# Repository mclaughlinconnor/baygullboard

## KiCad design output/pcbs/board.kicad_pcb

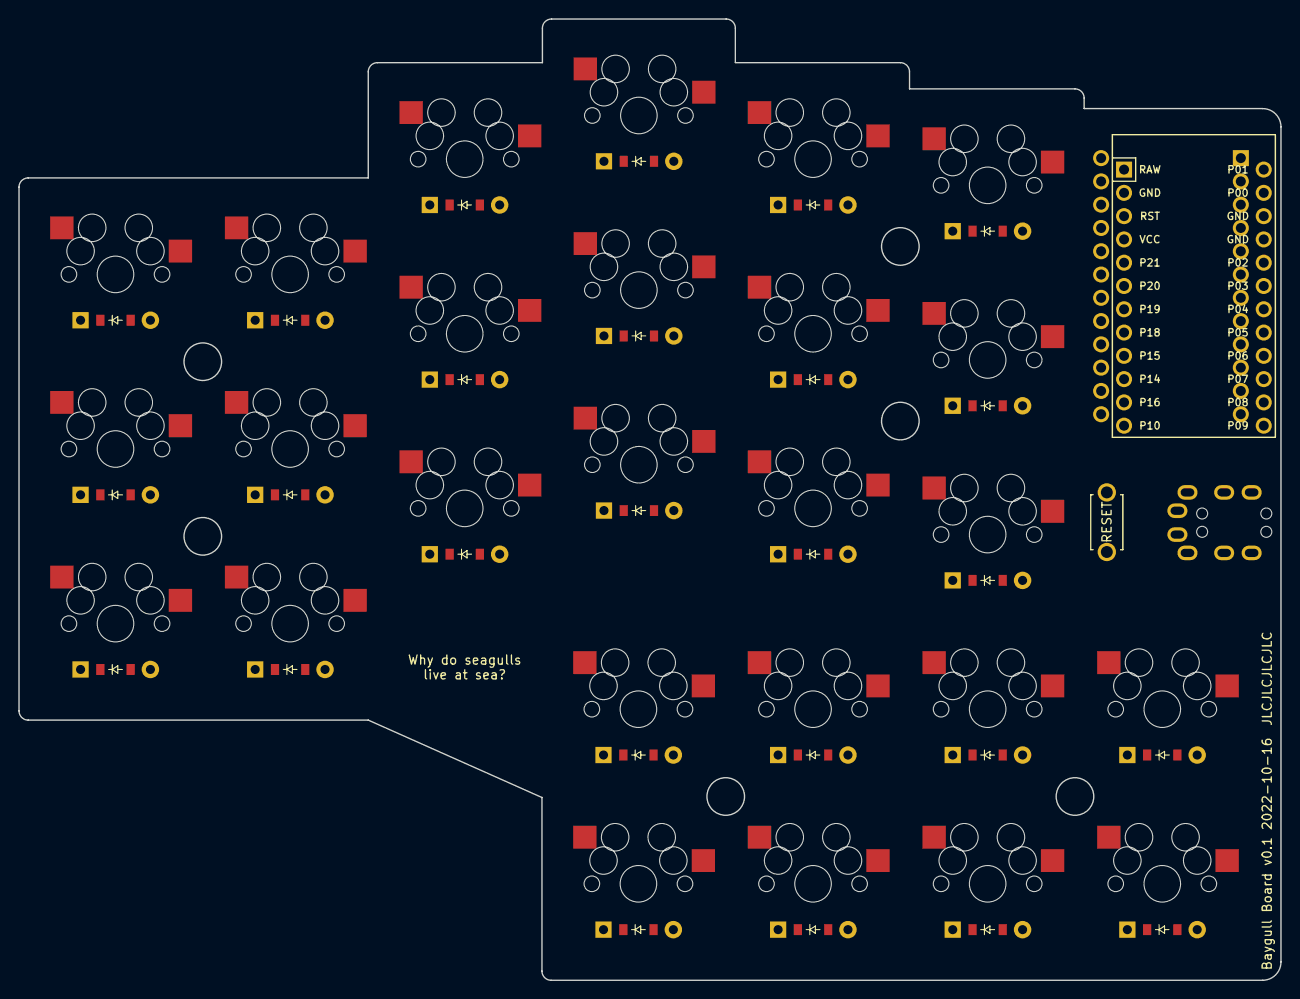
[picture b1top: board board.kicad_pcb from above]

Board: 2 copper layers, 137.7 x 104.9 mm, 57 parts (0 on the bottom side), 48 nets, no tracks yet.

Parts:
B1: ResetSW
D1, D2, D3, D4, D5, D6, D7, D8, D9, D10, D11, D12, D13, D14, D15, D16, D17, D18, D19, D20, D21, D22, D23, D24, D25, D26: ComboDiode
MCU1, MCU2: ProMicro
S1, S2, S3, S4, S5, S6, S7, S8, S9, S10, S11, S12, S13, S14, S15, S16, S17, S18, S19, S20, S21, S22, S23, S24, S25, S26: MX
TRRS1, TRRS2: TRRS-PJ-320A-dual

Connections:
GND: B1.2, MCU1.2, MCU1.15, MCU1.16, MCU2.2, MCU2.15, MCU2.16, TRRS1.3, TRRS2.3
P0: MCU1.14, MCU2.14, TRRS1.4, TRRS2.4
P1: MCU1.13, MCU2.13
P2: MCU1.17, MCU2.17
P3: MCU1.18, MCU2.18
P4: D3.1, D3.2, D6.1, D6.2, D9.1, D9.2, D12.1, D12.2, D15.1, D15.2, D18.1, D18.2, MCU1.19, MCU2.19
P5: D2.1, D2.2, D5.1, D5.2, D8.1, D8.2, D11.1, D11.2, D14.1, D14.2, D17.1, D17.2, MCU1.20, MCU2.20
P6: D1.1, D1.2, D4.1, D4.2, D7.1, D7.2, D10.1, D10.2, D13.1, D13.2, D16.1, D16.2, MCU1.21, MCU2.21
P7: D19.1, D19.2, D20.1, D20.2, D21.1, D21.2, D22.1, D22.2, D23.1, D23.2, D24.1, D24.2, D25.1, D25.2, D26.1, D26.2, MCU1.22, MCU2.22
P8: MCU1.23, MCU2.23
P9: MCU1.24, MCU2.24
P10: MCU1.12, MCU2.12
P14: MCU1.10, MCU2.10, S16.2, S17.2, S18.2, S24.2
P15: MCU1.9, MCU2.9, S13.2, S14.2, S15.2, S23.2
P16: MCU1.11, MCU2.11
P18: MCU1.8, MCU2.8, S10.2, S11.2, S12.2, S19.2, S20.2
P19: MCU1.7, MCU2.7, S7.2, S8.2, S9.2, S21.2, S22.2
P20: MCU1.6, MCU2.6, S4.2, S5.2, S6.2, S25.2
P21: MCU1.5, MCU2.5, S1.2, S2.2, S3.2, S26.2
RAW: MCU1.1, MCU2.1
RST: B1.1, MCU1.3, MCU2.3
VCC: MCU1.4, MCU2.4, TRRS1.2, TRRS2.2
four_a_thumb: D25.1, D25.2, S25.1
four_b_thumb: D26.1, D26.2, S26.1
index_bottom: D13.1, D13.2, S13.1
index_home: D14.1, D14.2, S14.1
index_top: D15.1, D15.2, S15.1
inner_bottom: D16.1, D16.2, S16.1
inner_home: D17.1, D17.2, S17.1
inner_top: D18.1, D18.2, S18.1
left_bottom: D1.1, D1.2, S1.1
left_home: D2.1, D2.2, S2.1
left_top: D3.1, D3.2, S3.1
middle_bottom: D10.1, D10.2, S10.1
middle_home: D11.1, D11.2, S11.1
middle_top: D12.1, D12.2, S12.1
one_a_thumb: D19.1, D19.2, S19.1
one_b_thumb: D20.1, D20.2, S20.1
pinky_bottom: D4.1, D4.2, S4.1
pinky_home: D5.1, D5.2, S5.1
pinky_top: D6.1, D6.2, S6.1
ring_bottom: D7.1, D7.2, S7.1
ring_home: D8.1, D8.2, S8.1
ring_top: D9.1, D9.2, S9.1
three_a_thumb: D23.1, D23.2, S23.1
three_b_thumb: D24.1, D24.2, S24.1
two_a_thumb: D21.1, D21.2, S21.1
two_b_thumb: D22.1, D22.2, S22.1

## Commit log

2022-11-19 Initial
2022-11-19 Add images
2022-11-19 Move images to right folder
2022-11-19 Remove images from old folder
2022-11-19 Initial readme
